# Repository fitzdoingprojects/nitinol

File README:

userful links:
    http://www.talkingelectronics.com/projects/Nitinol/Nitinol-3.html

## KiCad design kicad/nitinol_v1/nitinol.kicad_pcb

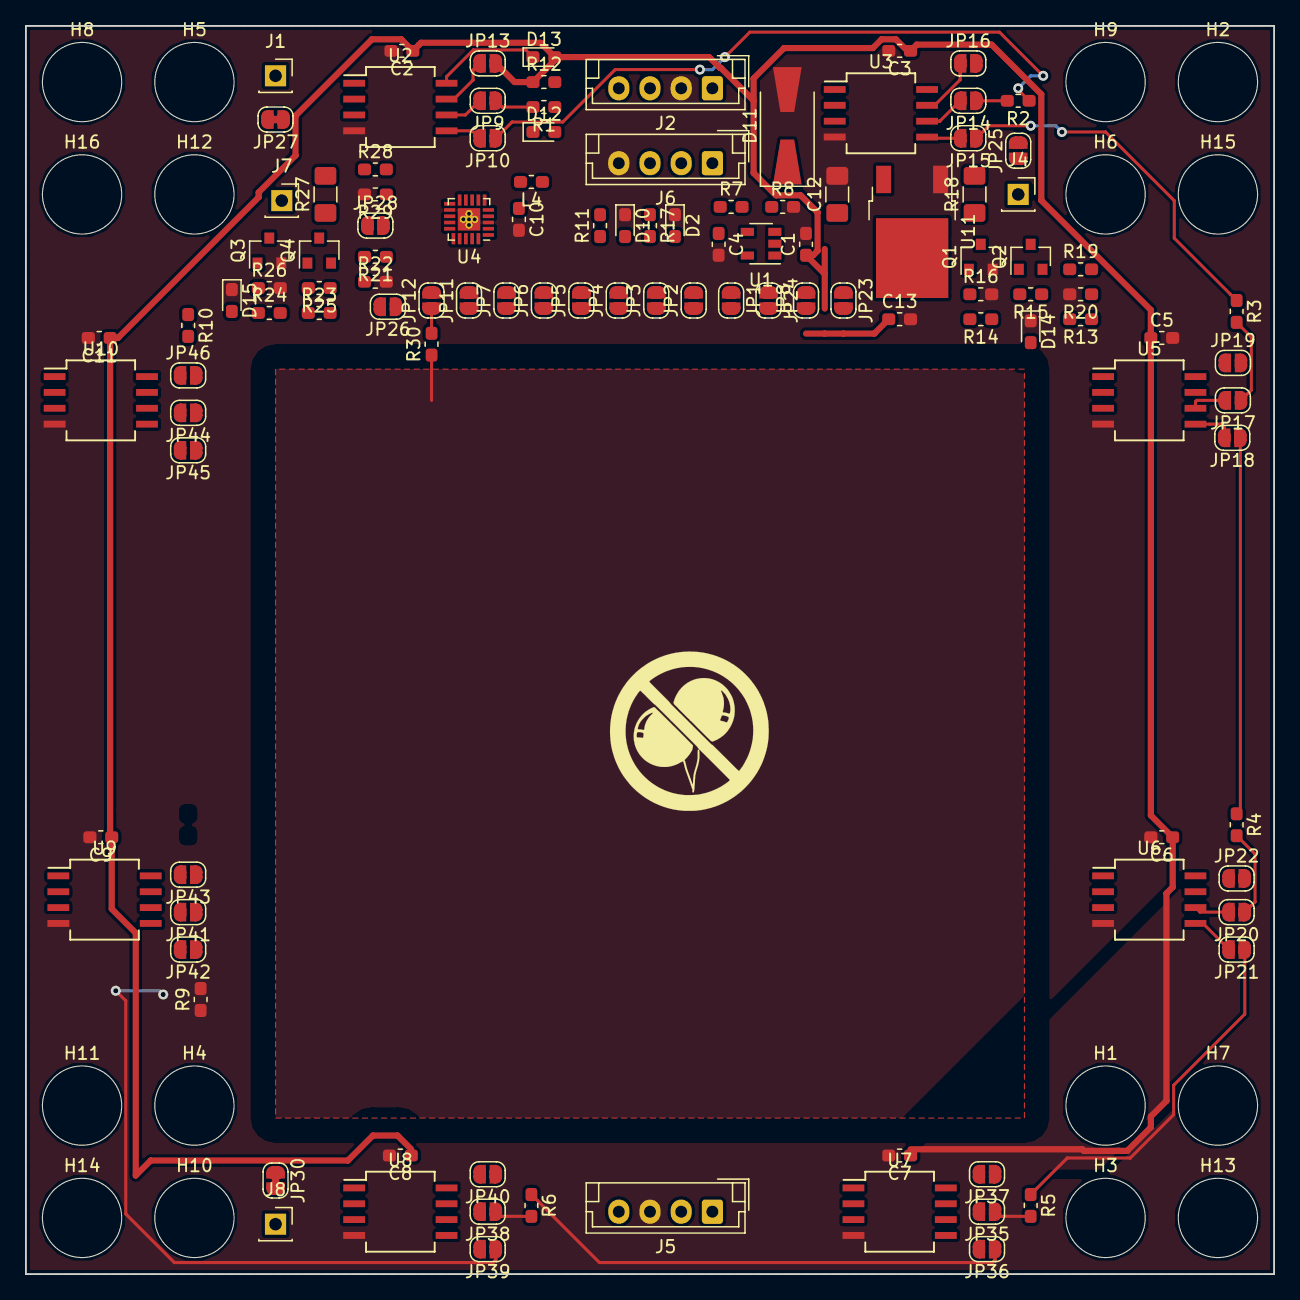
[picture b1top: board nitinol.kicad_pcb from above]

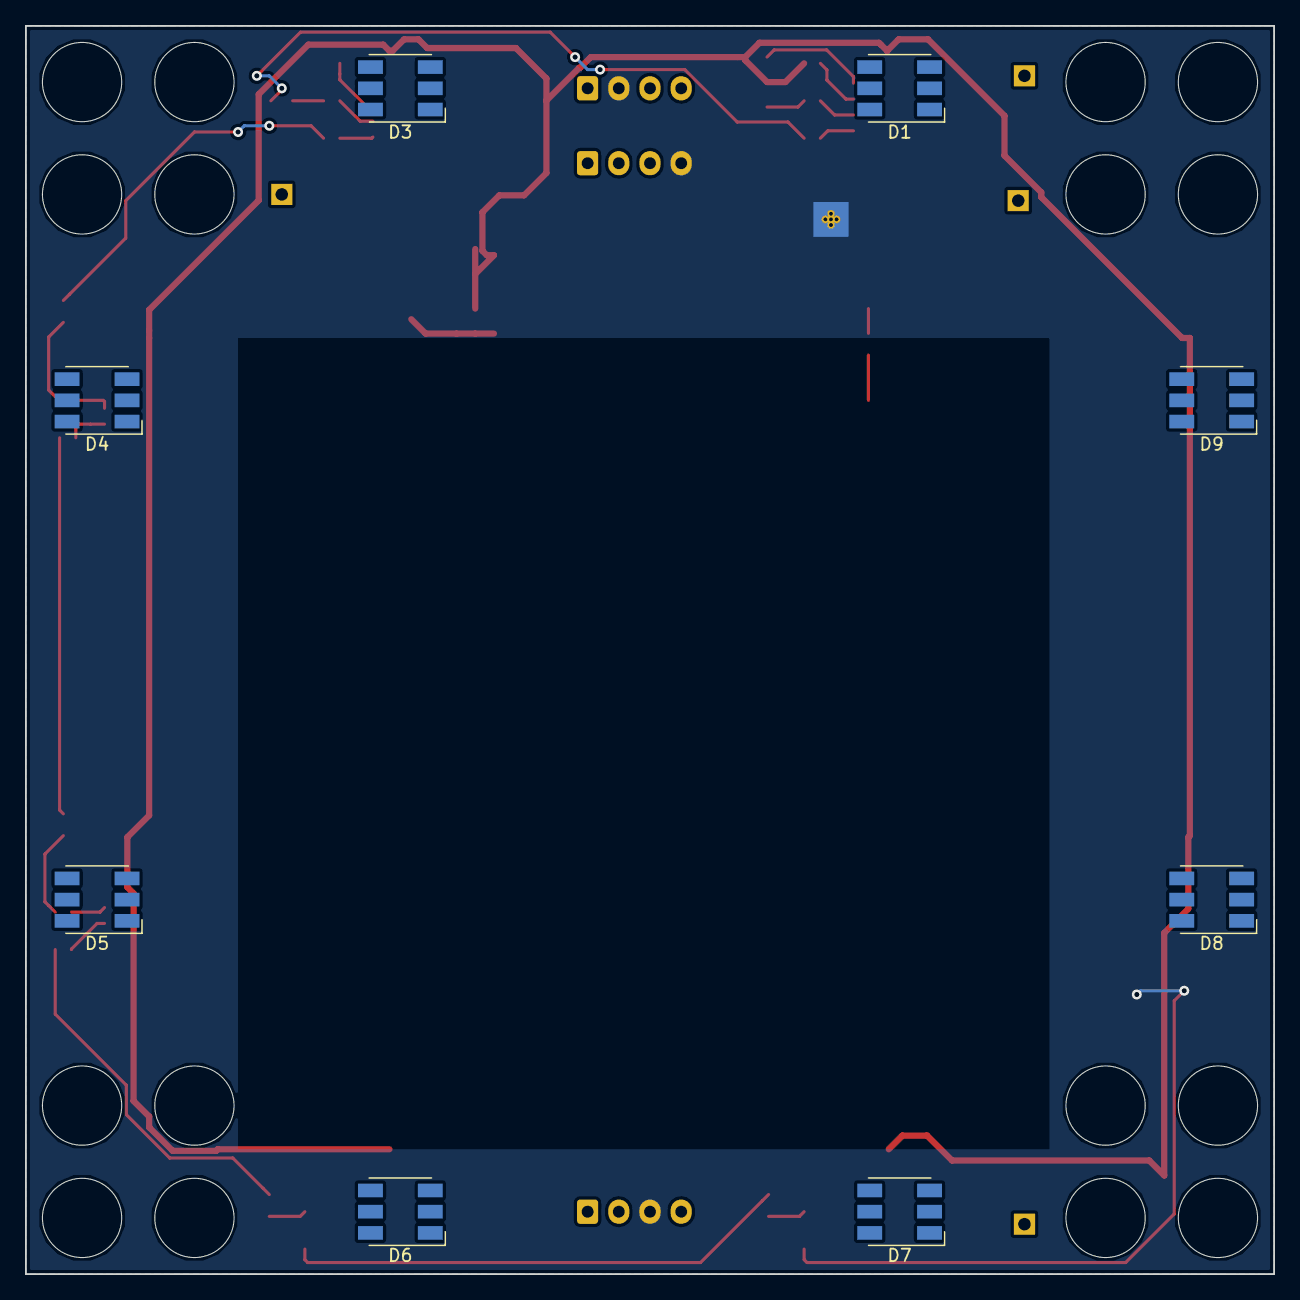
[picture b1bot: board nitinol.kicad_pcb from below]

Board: 2 copper layers, 100.0 x 100.0 mm, 139 parts (8 on the bottom side), 110 nets.

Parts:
C1, C4, C13: 10uF; C_0603_1608Metric_Pad1.05x0.95mm_HandSolder
C2, C3, C5, C6, C7, C8, C9, C10, C11: 0.1uF; C_0603_1608Metric_Pad1.05x0.95mm_HandSolder
C12: 10uF; C_1206_3216Metric_Pad1.42x1.75mm_HandSolder
D1, D3, D4, D5, D6, D7, D8, D9: LED_RGB; LED_RGB_5050-6
D2: GREEN; LED_0603_1608Metric_Pad1.05x0.95mm_HandSolder
D10: BLUE; LED_0603_1608Metric_Pad1.05x0.95mm_HandSolder
D11: 1N5819; D_SMA-SMB_Universal_Handsoldering
D12, D13: JUMPER; D_0603_1608Metric_Pad1.05x0.95mm_HandSolder
D14, D15: RED; LED_0603_1608Metric_Pad1.05x0.95mm_HandSolder
H1, H2, H3, H4, H5, H6, H7, H8, H9, H10, H11, H12, H13, H14, H15, H16: MountingHole; Grommet_0.25in_1061T11
J1: NITINOL_1-; PinSocket_1x01_P2.54mm_Vertical
J2: IN; JST_EH_B04B-EH-A_1x04_P2.50mm_Vertical
J4: NITINOL_1+; PinSocket_1x01_P2.54mm_Vertical
J5: OUT; JST_EH_B04B-EH-A_1x04_P2.50mm_Vertical
J6: PRGM; JST_EH_B04B-EH-A_1x04_P2.50mm_Vertical
J7: NITINOL_2+; PinSocket_1x01_P2.54mm_Vertical
J8: NITINOL_2-; PinSocket_1x01_P2.54mm_Vertical
JP1, JP2, JP3, JP4, JP5, JP6, JP7, JP8, JP9, JP10, JP11, JP12, JP13, JP14, JP15, JP16, JP17, JP18, JP19, JP20, JP21, JP22, JP23, JP24, JP25, JP26, JP28, JP35, JP36, JP37, JP38, JP39, JP40, JP41, JP42, JP43, JP44, JP45, JP46: Jumper_NO_Small; SolderJumper-2_P1.3mm_Open_RoundedPad1.0x1.5mm
JP27, JP30: Jumper_NC_Small; SolderJumper-2_P1.3mm_Bridged_RoundedPad1.0x1.5mm
L4: L_Core_Ferrite_Small; L_0603_1608Metric_Pad1.05x0.95mm_HandSolder
Q1, Q3: MMBT3904; SOT-23
Q2, Q4: AO3401; SOT-23
R1, R2, R3, R4, R5, R6, R9, R10: 33R; R_0603_1608Metric_Pad1.05x0.95mm_HandSolder
R7: 16K 1%; R_0603_1608Metric_Pad1.05x0.95mm_HandSolder
R8, R15, R16, R19, R20, R21, R22, R25, R26, R28, R29: 10K 1%; R_0603_1608Metric_Pad1.05x0.95mm_HandSolder
R11, R13, R17, R23: 100K; R_0603_1608Metric_Pad1.05x0.95mm_HandSolder
R12: NC; R_0603_1608Metric_Pad1.05x0.95mm_HandSolder
R14, R24, R30: 1K; R_0603_1608Metric_Pad1.05x0.95mm_HandSolder
R18, R27: 1R; R_1206_3216Metric_Pad1.42x1.75mm_HandSolder
SYM1: SYM_Radioactive_Radiation_Small; logo_large
U1: AP2127K-3.3; SOT-23-5
U2, U3, U5, U6, U7, U8, U9, U10: WS2811; SO-8_5.3x6.2mm_P1.27mm
U4: EFM8BB10F2G-A-QFN20; SiliconLabs_QFN-20-1EP_3x3mm_P0.5mm_ThermalVias
U11: LM1117-5.0; TO-252-2

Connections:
+3V3: J6.1, JP1.2, JP24.1, L4.1
+5V: C1.1, C2.1, C3.1, C5.1, C6.1, C7.1, C8.1, C9.1, C11.1, C13.1, D1.4, D1.5, D1.6, D3.4, D3.5, D3.6, D4.4, D4.5, D4.6, D5.4, D5.5, D5.6, D6.4, D6.5, D6.6, D7.4, D7.5, D7.6, D8.4, D8.5, D8.6, D9.4, D9.5, D9.6, D13.2, JP8.1, JP13.2, JP16.2, JP19.2, JP22.2, JP23.2, JP37.2, JP40.2, JP43.2, JP46.2, R12.1, U1.1, U3.8, U5.8, U6.8, U7.8, U8.8, U9.8, U10.8, U11.2
/C2CK: J6.2, U4.5
/C2D: J6.3, U4.6
/DATA: D12.1, JP11.1
/DI: J2.3, J5.2, JP6.1
/DO: J2.4, J5.1, JP7.1
/N1_a: JP25.1, Q2.2, R15.1
/N1_b: Q2.3, R18.1
/N1_d: J1.1, JP27.2
/N2_a: JP28.1, Q4.2, R25.1
/N2_b: Q4.3, R27.1
/N2_c: J4.1, J7.1, R18.2, R19.1, R27.2, R28.1
/N2_d: J8.1, JP30.2
/NITINOL_1: JP2.1, R13.1, R14.2
/NITINOL_2: JP4.1, R23.1, R24.2
/P0.0: JP2.2, U4.2
/P0.1: JP3.2, U4.1
/P0.2: JP4.2, U4.20
/P0.3: JP5.2, U4.19
/P0.4: JP6.2, U4.18
/P0.5: JP7.2, U4.17
/P0.6: JP11.2, U4.16
/P0.7: JP12.2, U4.15
/P1.0: JP26.1, U4.14
/P1.1: R11.1, U4.13
/SENSE_1: JP3.1, R19.2, R20.1
/SENSE_2: JP5.1, R28.2, R29.1
/TOUCH: JP12.1, R30.2
GND: C1.2, C2.2, C3.2, C4.2, C5.2, C6.2, C7.2, C8.2, C9.2, C10.2, C11.2, C12.2, C13.2, D2.1, D10.1, D11.2, D14.1, D15.1, J2.2, J5.3, J6.4, JP27.1, JP30.1, Q1.2, Q3.2, R8.2, R16.2, R20.2, R22.2, R26.2, R29.2, U2.4, U3.4, U4.3, U4.12, U4.21, U5.4, U6.4, U7.4, U8.4, U9.4, U10.4, U11.1
unnamed: C4.1, JP1.1, R7.1, U1.5
unnamed: C10.1, L4.2, U4.4
unnamed: D1.1, U2.1
unnamed: D1.2, U2.2
unnamed: D1.3, U2.3
unnamed: D2.2, R17.2
unnamed: D3.1, U3.1
unnamed: D3.2, U3.2
unnamed: D3.3, U3.3
unnamed: D4.1, U5.1
unnamed: D4.2, U5.2
unnamed: D4.3, U5.3
unnamed: D5.1, U6.1
unnamed: D5.2, U6.2
unnamed: D5.3, U6.3
unnamed: D6.1, U7.1
unnamed: D6.2, U7.2
unnamed: D6.3, U7.3
unnamed: D7.1, U8.1
unnamed: D7.2, U8.2
unnamed: D7.3, U8.3
unnamed: D8.1, U9.1
unnamed: D8.2, U9.2
unnamed: D8.3, U9.3
unnamed: D9.1, U10.1
unnamed: D9.2, U10.2
unnamed: D9.3, U10.3
unnamed: D10.2, R11.2
unnamed: D12.2, R1.1, R12.2
unnamed: D13.1, U2.8
unnamed: D14.2, R13.2
unnamed: D15.2, R23.2
unnamed: JP8.2, U1.3
unnamed: JP9.1, R1.2
unnamed: JP9.2, U2.6
unnamed: JP10.1, R2.1
unnamed: JP10.2, U2.5
unnamed: JP13.1, U2.7
unnamed: JP14.1, R2.2
unnamed: JP14.2, U3.6
unnamed: JP15.1, R3.1
unnamed: JP15.2, U3.5
unnamed: JP16.1, U3.7
unnamed: JP17.1, R3.2
unnamed: JP17.2, U5.6
unnamed: JP18.1, R4.1
unnamed: JP18.2, U5.5
unnamed: JP19.1, U5.7
unnamed: JP20.1, R4.2
unnamed: JP20.2, U6.6
unnamed: JP21.1, R5.1
unnamed: JP21.2, U6.5
unnamed: JP22.1, U6.7
unnamed: JP24.2, R17.1
unnamed: JP26.2, R21.2, R22.1
unnamed: JP35.1, R5.2
unnamed: JP35.2, U7.6
unnamed: JP36.1, R6.1
unnamed: JP36.2, U7.5
unnamed: JP37.1, U7.7
unnamed: JP38.1, R6.2
unnamed: JP38.2, U8.6
unnamed: JP39.1, R9.1
unnamed: JP39.2, U8.5
unnamed: JP40.1, U8.7
unnamed: JP41.1, R9.2
unnamed: JP41.2, U9.6
unnamed: JP42.1, R10.1
unnamed: JP42.2, U9.5
unnamed: JP43.1, U9.7
unnamed: JP44.1, R10.2
unnamed: JP44.2, U10.6
unnamed: JP45.2, U10.5
unnamed: JP46.1, U10.7
unnamed: Q1.1, R14.1, R16.1
unnamed: Q1.3, Q2.1, R15.2
unnamed: Q3.1, R24.1, R26.1
unnamed: Q3.3, Q4.1, R25.2
unnamed: R7.2, R8.1, U1.2
VDD: C12.1, D11.1, J2.1, J5.4, JP23.1, JP25.2, JP28.2, R21.1, U11.3

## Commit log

2018-12-28 working schematic
2018-12-31 all components placed, starting on tracks
